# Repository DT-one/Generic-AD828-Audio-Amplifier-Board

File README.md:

## Documentation for Generic AD828 Amplifier Boards

These audio amplifier opamp boards are commonly available on sites like Amazon, Alibaba and eBay, but there does not seem to be any schematics for them.

They appear to use a classic AC coupled inverting amplifier design and provide some through holes for adding feedback resistors.

The circuit is relatively simple, but without documentation requires requires some reverse engineering to calculate what the feedback resistors should be for a given gain.

Here is an accurate recreation in KiCAD, including spice simulations and gain resistor settings.

Note that the listed resistors are added in parallel to the existing 20k SMD resistor (the listed resistance is not the actual feedback resistance)

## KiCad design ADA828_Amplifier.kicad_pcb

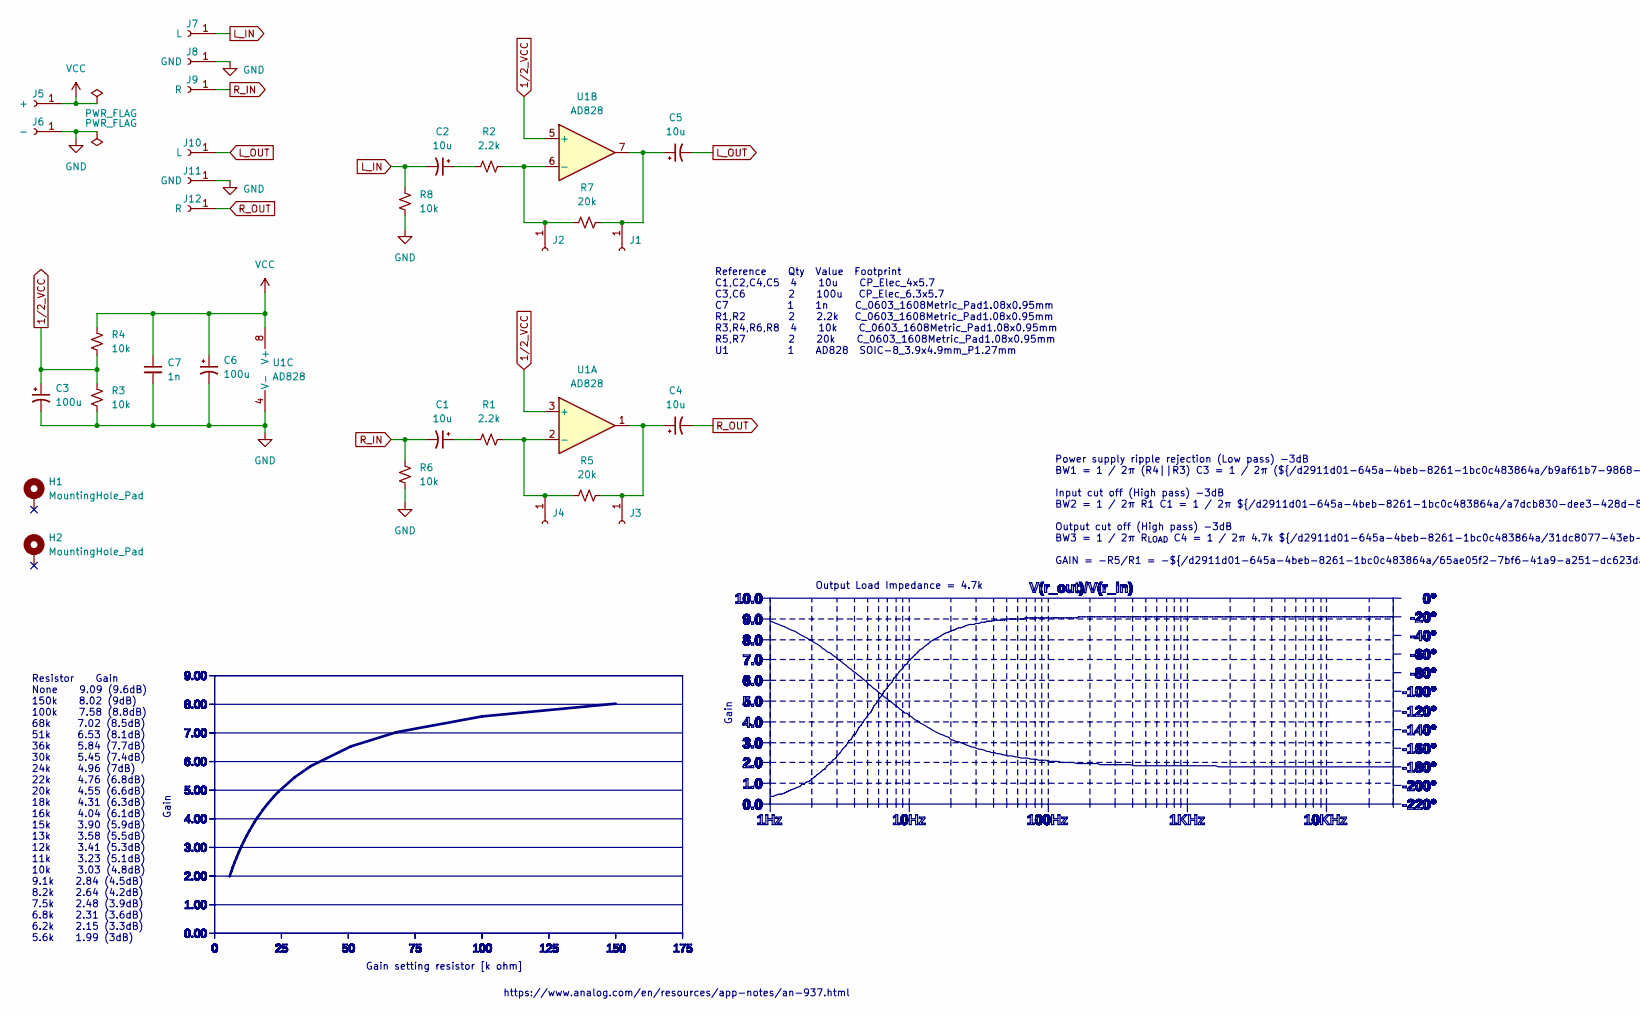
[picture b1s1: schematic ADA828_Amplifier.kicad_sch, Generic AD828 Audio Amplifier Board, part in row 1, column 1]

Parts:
C1, C2, C4, C5: 10u; CP_Elec_4x5.7
C3, C6: 100u; CP_Elec_6.3x5.7
C7: 1n; C_0603_1608Metric_Pad1.08x0.95mm_HandSolder
H1, H2: MountingHole_Pad; TestPoint_Plated_Hole_D3.5mm
J1, J2, J3, J4: Conn_01x01_Socket; TestPoint_THTPad_D2.0mm_Drill1.0mm
J5: +; TestPoint_THTPad_D2.0mm_Drill1.0mm
J6: -; TestPoint_THTPad_D2.0mm_Drill1.0mm
J7, J10: L; TestPoint_THTPad_D2.0mm_Drill1.0mm
J8, J11: GND; TestPoint_THTPad_D2.0mm_Drill1.0mm
J9, J12: R; TestPoint_THTPad_D2.0mm_Drill1.0mm
R1, R2: 2.2k; R_0603_1608Metric_Pad0.98x0.95mm_HandSolder
R3, R4, R6, R8: 10k; R_0603_1608Metric_Pad0.98x0.95mm_HandSolder
R5, R7: 20k; R_0603_1608Metric_Pad0.98x0.95mm_HandSolder
U1: AD828; SOIC-8_3.9x4.9mm_P1.27mm

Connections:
1/2_VCC: C3.1, R3.1, R4.2, U1.3 (+), U1.5 (+)
GND: C3.2, C6.2, C7.2, J6.1, J8.1, J11.1, R3.2, R6.2, R8.2, U1.4 (V-)
L_IN: C2.2, J7.1, R8.1
L_OUT: C5.2, J10.1
unnamed: C1.1, R1.2
unnamed: C2.1, R2.2
unnamed: C5.1, J1.1, R7.1, U1.7
unnamed: J2.1, R2.1, R7.2, U1.6 (-)
unnamed: C4.1, J3.1, R5.1, U1.1
unnamed: J4.1, R1.1, R5.2, U1.2 (-)
R_IN: C1.2, J9.1, R6.1
R_OUT: C4.2, J12.1
VCC: C6.1, C7.1, J5.1, R4.1, U1.8 (V+)

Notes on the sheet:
Power supply ripple rejection (Low pass) -3dB BW1 = 1 / 2π (R4||R3) C3 = 1 / 2π (${/d2911d01-645a-4beb-8261-1bc0c483864a/b9af61b7-9868-424c-a19b-94628b09d58a:value}||${/d2911d01-645a-4beb-8261-1bc0c483864a/655c2c68-45b3-4cb4-94c0-5e4d41aed458:value}) ${/d2911d01-645a-4beb-8261-1bc0c483864a/10caf2e7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
Output Load Impedance = 4.7k
Gain
Resistor Gain None 9.09 (9.6dB) 150k 8.02 (9dB) 100k 7.58 (8.8dB) 68k 7.02 (8.5dB) 51k 6.53 (8.1dB) 36k 5.84 (7.7dB) 30k 5.45 (7.4dB) 24k 4.96 (7dB) 22k 4.76 (6.8dB) 20k 4.55 (6.6dB) 18k 4.31 (6.3dB) 16k 4.04 (6.1dB) 15k 3.90 (5.9dB) 13k 3.58 (5.5dB) 12k 3.41 (5.3dB) 11k 3.23 (5.1dB) 10k 3.03 (4.8d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
https://www.analog.com/en/resources/app-notes/an-937.html
Reference Qty Value Footprint C1,C2,C4,C5 4 10u CP_Elec_4x5.7 C3,C6 2 100u CP_Elec_6.3x5.7 C7 1 1n C_0603_1608Metric_Pad1.08x0.95mm R1,R2 2 2.2k C_0603_1608Metric_Pad1.08x0.95mm R3,R4,R6,R8 4 10k C_0603_1608Metric_Pad1.08x0.95mm R5,R7 2 20k C_0603_1608Metric_Pad1.08x0.95mm U1 1 AD828 SOIC-8_3.9x4.9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
Gain setting resistor [k ohm]

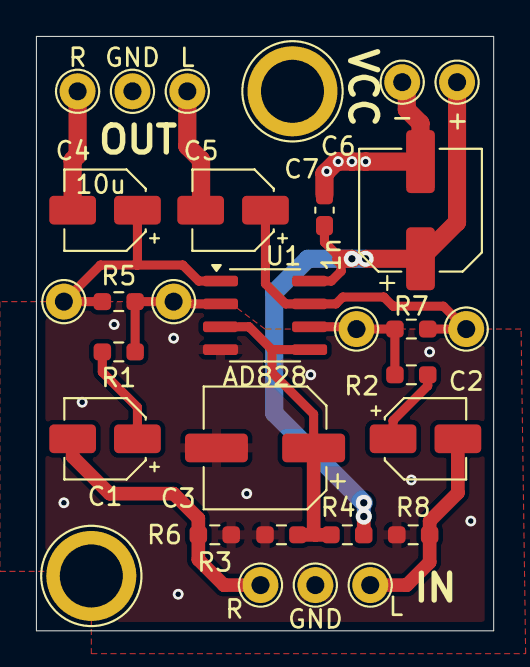
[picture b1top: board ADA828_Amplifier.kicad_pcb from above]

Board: 2 copper layers, 25.4 x 33.0 mm, 30 parts (0 on the bottom side), 13 nets.
